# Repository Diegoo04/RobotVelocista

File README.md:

# RobotVelocista
Robot velocista /// Race robot ///
Placa frontal:
-Primer día:
  Hoy hemos hecho el esquema de la placa de los sensores y hemos empezado a hacer la PCB.🏎🔥
-Segundo día:
  Hoy he enrutado las redes y ahora estoy nombrando los pines en la placa.✏
-Tercer día:
  Hoy he terminado de nombrar los pines de la pcb.
Placa principal:
-Tercer día:
  Hoy hemos empezado el esquema de los modulos de la placa(Microconector,Conectores auxiliares) y he hecho los flags.

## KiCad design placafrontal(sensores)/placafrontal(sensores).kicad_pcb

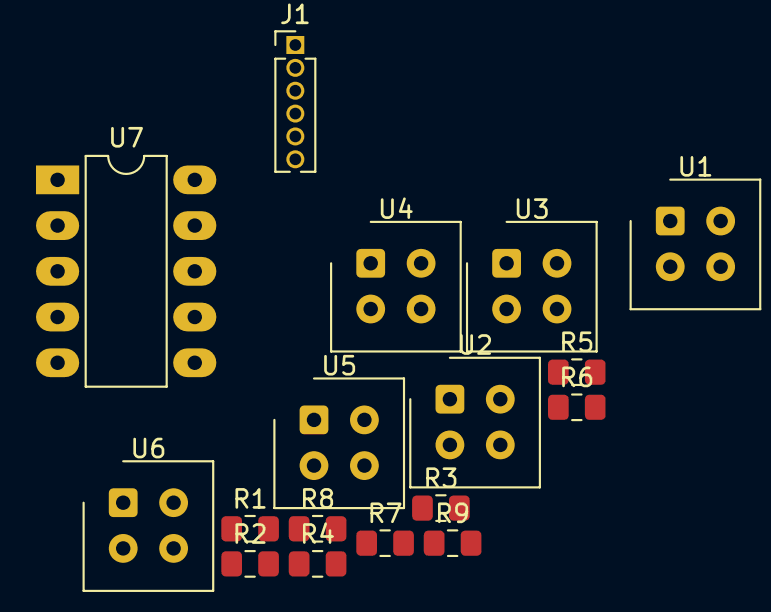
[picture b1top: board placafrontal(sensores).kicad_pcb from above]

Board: 2 copper layers, 17 parts (0 on the bottom side), 16 nets, no tracks yet.

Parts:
J1: Conn_01x06_Female; PinHeader_1x06_P1.27mm_Vertical
R1, R4, R7: 82; R_0805_2012Metric_Pad1.15x1.40mm_HandSolder
R2, R3, R5, R6, R8, R9: 10k; R_0805_2012Metric_Pad1.15x1.40mm_HandSolder
U1, U2, U3, U4, U5, U6: CNY70; Vishay_CNY70
U7: 4053; DIP-10_W7.62mm_LongPads

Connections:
+5V: J1.1, R2.1, R3.1, R5.1, R6.1, R8.1, R9.1, U1.1, U3.1, U5.1
/linea3: J1.5, U7.4
/linea_selec: U7.9, U7.10
/sensor1: R2.2, U1.3
/sensor2: R3.2, U2.3
/sensor3: R5.2, U3.3, U7.2
/sensor4: R6.2, U4.3, U7.1
/sensor5: R8.2, U5.3, U7.5
/sensor6: R9.2, U6.3, U7.3
GND: J1.2, U1.4, U2.2, U2.4, U3.4, U4.2, U4.4, U5.4, U6.2, U6.4, U7.6, U7.7, U7.8
unnamed: R1.1, U1.2
unnamed: R1.2, U2.1
unnamed: R4.1, U3.2
unnamed: R4.2, U4.1
unnamed: R7.1, U5.2
unnamed: R7.2, U6.1
